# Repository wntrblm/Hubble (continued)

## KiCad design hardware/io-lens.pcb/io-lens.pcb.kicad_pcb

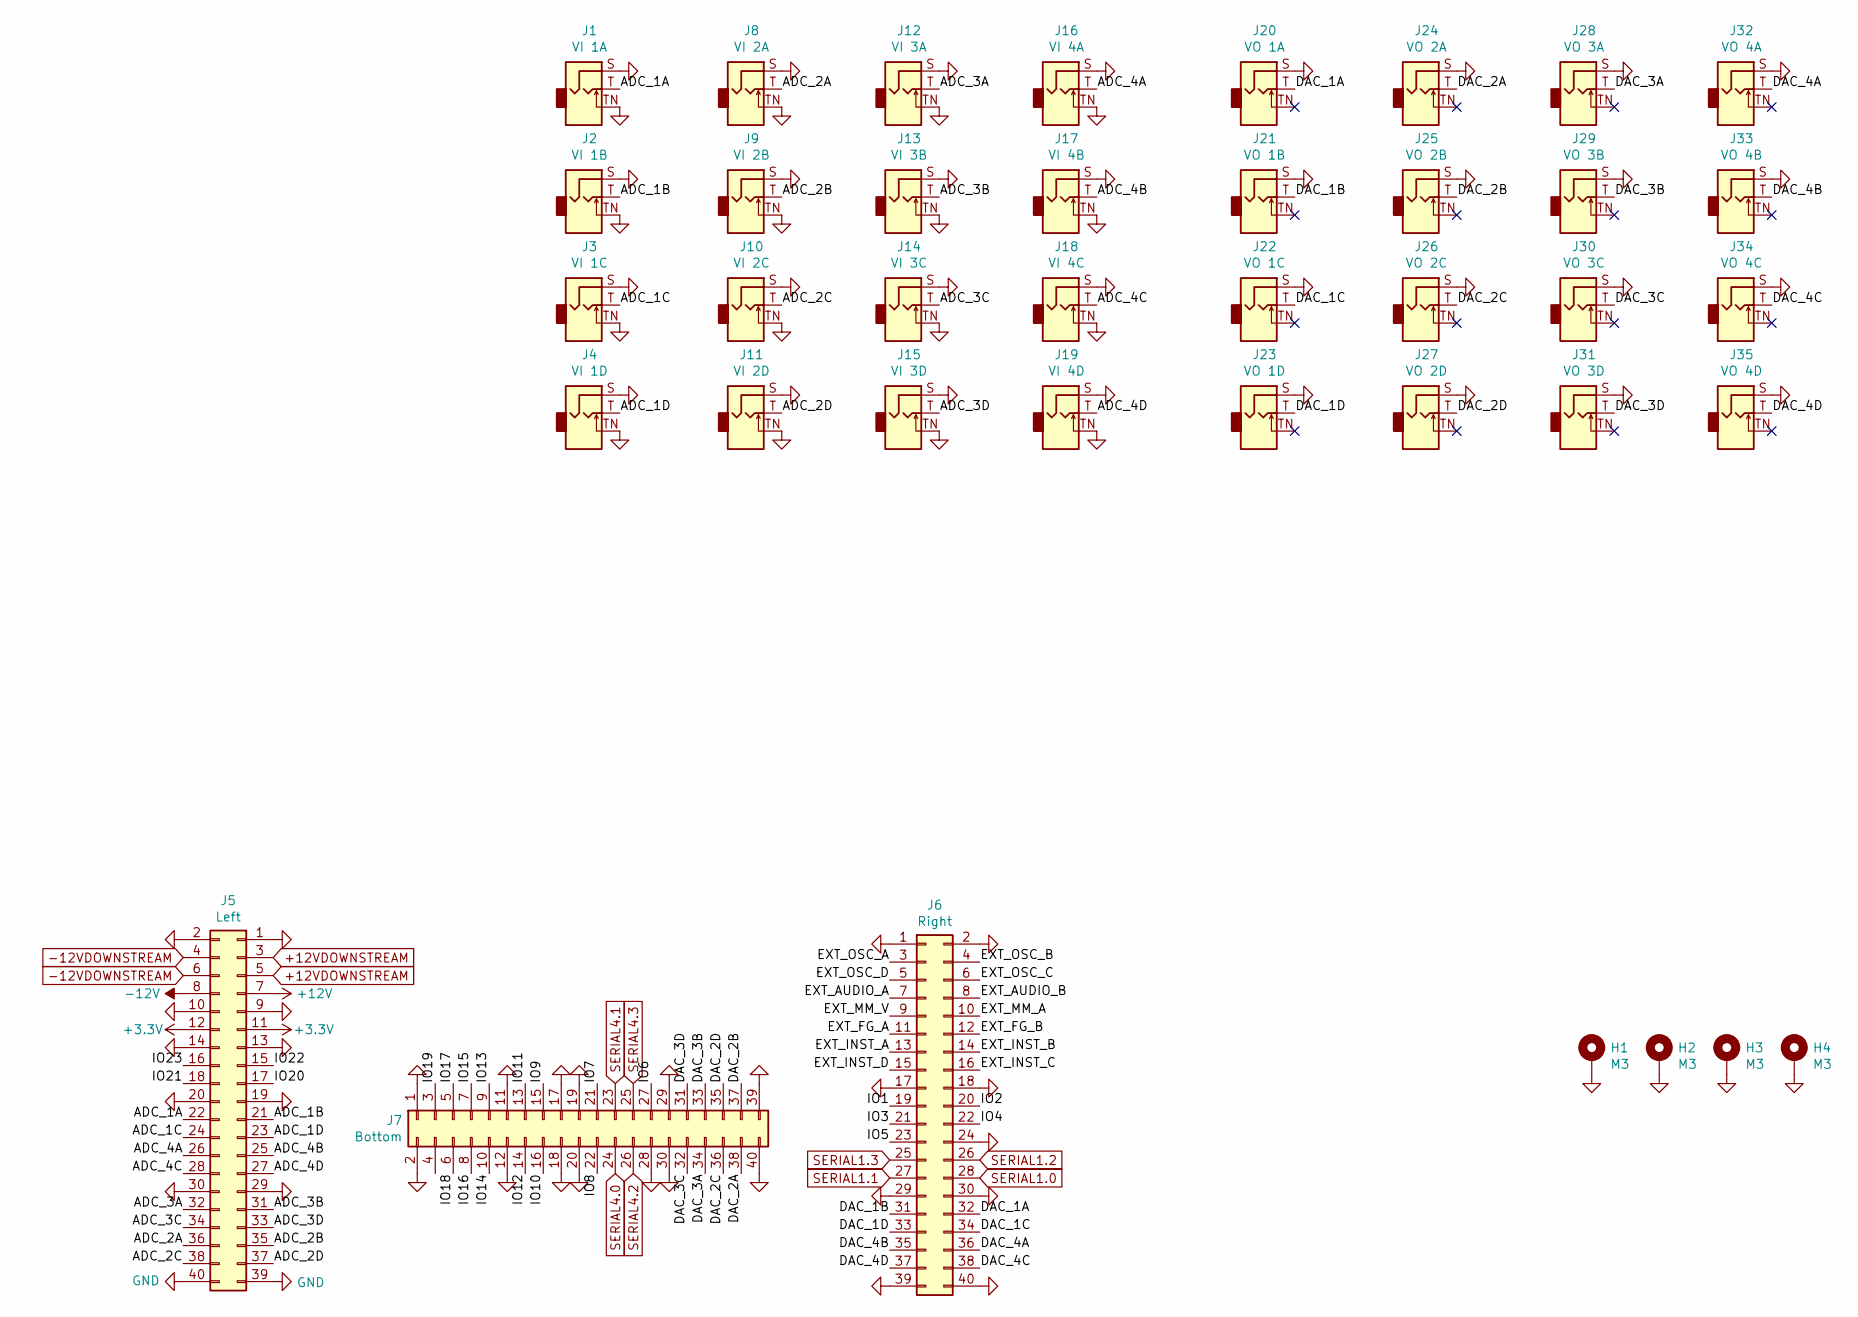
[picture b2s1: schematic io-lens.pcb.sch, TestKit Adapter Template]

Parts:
H1, H2, H3, H4: M3; MountingHole_3.2mm_M3_Pad_Via
J1: VI 1A; WQP-WQP518MA; mpn WQP-WQP518MA
J2: VI 1B; WQP-WQP518MA; mpn WQP-WQP518MA
J3: VI 1C; WQP-WQP518MA; mpn WQP-WQP518MA
J4: VI 1D; WQP-WQP518MA; mpn WQP-WQP518MA
J5: Left; PinSocket_2x20_P2.54mm_Vertical
J6: Right; PinSocket_2x20_P2.54mm_Vertical
J7: Bottom; PinSocket_2x20_P2.54mm_Vertical
J8: VI 2A; WQP-WQP518MA; mpn WQP-WQP518MA
J9: VI 2B; WQP-WQP518MA; mpn WQP-WQP518MA
J10: VI 2C; WQP-WQP518MA; mpn WQP-WQP518MA
J11: VI 2D; WQP-WQP518MA; mpn WQP-WQP518MA
J12: VI 3A; WQP-WQP518MA; mpn WQP-WQP518MA
J13: VI 3B; WQP-WQP518MA; mpn WQP-WQP518MA
J14: VI 3C; WQP-WQP518MA; mpn WQP-WQP518MA
J15: VI 3D; WQP-WQP518MA; mpn WQP-WQP518MA
J16: VI 4A; WQP-WQP518MA; mpn WQP-WQP518MA
J17: VI 4B; WQP-WQP518MA; mpn WQP-WQP518MA
J18: VI 4C; WQP-WQP518MA; mpn WQP-WQP518MA
J19: VI 4D; WQP-WQP518MA; mpn WQP-WQP518MA
J20: VO 1A; WQP-WQP518MA; mpn WQP-WQP518MA
J21: VO 1B; WQP-WQP518MA; mpn WQP-WQP518MA
J22: VO 1C; WQP-WQP518MA; mpn WQP-WQP518MA
J23: VO 1D; WQP-WQP518MA; mpn WQP-WQP518MA
J24: VO 2A; WQP-WQP518MA; mpn WQP-WQP518MA
J25: VO 2B; WQP-WQP518MA; mpn WQP-WQP518MA
J26: VO 2C; WQP-WQP518MA; mpn WQP-WQP518MA
J27: VO 2D; WQP-WQP518MA; mpn WQP-WQP518MA
J28: VO 3A; WQP-WQP518MA; mpn WQP-WQP518MA
J29: VO 3B; WQP-WQP518MA; mpn WQP-WQP518MA
J30: VO 3C; WQP-WQP518MA; mpn WQP-WQP518MA
J31: VO 3D; WQP-WQP518MA; mpn WQP-WQP518MA
J32: VO 4A; WQP-WQP518MA; mpn WQP-WQP518MA
J33: VO 4B; WQP-WQP518MA; mpn WQP-WQP518MA
J34: VO 4C; WQP-WQP518MA; mpn WQP-WQP518MA
J35: VO 4D; WQP-WQP518MA; mpn WQP-WQP518MA

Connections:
+3V3: J5.11, J5.12
+12V: J5.7
+12VDOWNSTREAM: J5.3, J5.5
-12V: J5.8
-12VDOWNSTREAM: J5.4, J5.6
/ADC_1A: J1.T (Tip), J5.22
/ADC_1B: J2.T (Tip), J5.21
/ADC_1C: J3.T (Tip), J5.24
/ADC_1D: J4.T (Tip), J5.23
/ADC_2A: J5.36, J8.T (Tip)
/ADC_2B: J5.35, J9.T (Tip)
/ADC_2C: J5.38, J10.T (Tip)
/ADC_2D: J5.37, J11.T (Tip)
/ADC_3A: J5.32, J12.T (Tip)
/ADC_3B: J5.31, J13.T (Tip)
/ADC_3C: J5.34, J14.T (Tip)
/ADC_3D: J5.33, J15.T (Tip)
/ADC_4A: J5.26, J16.T (Tip)
/ADC_4B: J5.25, J17.T (Tip)
/ADC_4C: J5.28, J18.T (Tip)
/ADC_4D: J5.27, J19.T (Tip)
/DAC_1A: J6.32, J20.T (Tip)
/DAC_1B: J6.31, J21.T (Tip)
/DAC_1C: J6.34, J22.T (Tip)
/DAC_1D: J6.33, J23.T (Tip)
/DAC_2A: J7.38, J24.T (Tip)
/DAC_2B: J7.37, J25.T (Tip)
/DAC_2C: J7.36, J26.T (Tip)
/DAC_2D: J7.35, J27.T (Tip)
/DAC_3A: J7.34, J28.T (Tip)
/DAC_3B: J7.33, J29.T (Tip)
/DAC_3C: J7.32, J30.T (Tip)
/DAC_3D: J7.31, J31.T (Tip)
/DAC_4A: J6.36, J32.T (Tip)
/DAC_4B: J6.35, J33.T (Tip)
/DAC_4C: J6.38, J34.T (Tip)
/DAC_4D: J6.37, J35.T (Tip)
/EXT_AUDIO_A: J6.7
/EXT_AUDIO_B: J6.8
/EXT_FG_A: J6.11
/EXT_FG_B: J6.12
/EXT_INST_A: J6.13
/EXT_INST_B: J6.14
/EXT_INST_C: J6.16
/EXT_INST_D: J6.15
/EXT_MM_A: J6.10
/EXT_MM_V: J6.9
/EXT_OSC_A: J6.3
/EXT_OSC_B: J6.4
/EXT_OSC_C: J6.6
/EXT_OSC_D: J6.5
/IO1: J6.19
/IO2: J6.20
/IO3: J6.21
/IO4: J6.22
/IO5: J6.23
/IO6: J7.27
/IO7: J7.21
/IO8: J7.22
/IO9: J7.15
/IO10: J7.16
/IO11: J7.13
/IO12: J7.14
/IO13: J7.9
/IO14: J7.10
/IO15: J7.7
/IO16: J7.8
/IO17: J7.5
/IO18: J7.6
/IO19: J7.3
/IO20: J5.17
/IO21: J5.18
/IO22: J5.15
/IO23: J5.16
GND: H1.1, H2.1, H3.1, H4.1, J1.S (Sleeve), J1.TN (Tip_normalize), J2.S (Sleeve), J2.TN (Tip_normalize), J3.S (Sleeve), J3.TN (Tip_normalize), J4.S (Sleeve), J4.TN (Tip_normalize), J5.1, J5.2, J5.9, J5.10, J5.13, J5.14, J5.19, J5.20, J5.29, J5.30, J5.39, J5.40, J6.1, J6.2, J6.17, J6.18, J6.24, J6.29, J6.30, J6.39, J6.40, J7.1, J7.2, J7.11, J7.12, J7.17, J7.18, J7.19, J7.20, J7.28, J7.29, J7.30, J7.39, J7.40, J8.S (Sleeve), J8.TN (Tip_normalize), J9.S (Sleeve), J9.TN (Tip_normalize), J10.S (Sleeve), J10.TN (Tip_normalize), J11.S (Sleeve), J11.TN (Tip_normalize), J12.S (Sleeve), J12.TN (Tip_normalize), J13.S (Sleeve), J13.TN (Tip_normalize), J14.S (Sleeve), J14.TN (Tip_normalize), J15.S (Sleeve), J15.TN (Tip_normalize), J16.S (Sleeve), J16.TN (Tip_normalize), J17.S (Sleeve), J17.TN (Tip_normalize), J18.S (Sleeve), J18.TN (Tip_normalize), J19.S (Sleeve), J19.TN (Tip_normalize), J20.S (Sleeve), J21.S (Sleeve), J22.S (Sleeve), J23.S (Sleeve), J24.S (Sleeve), J25.S (Sleeve), J26.S (Sleeve), J27.S (Sleeve), J28.S (Sleeve), J29.S (Sleeve), J30.S (Sleeve), J31.S (Sleeve), J32.S (Sleeve), J33.S (Sleeve), J34.S (Sleeve), J35.S (Sleeve)
SERIAL1.0: J6.28
SERIAL1.1: J6.27
SERIAL1.2: J6.26
SERIAL1.3: J6.25
SERIAL4.0: J7.24
SERIAL4.1: J7.23
SERIAL4.2: J7.26
SERIAL4.3: J7.25

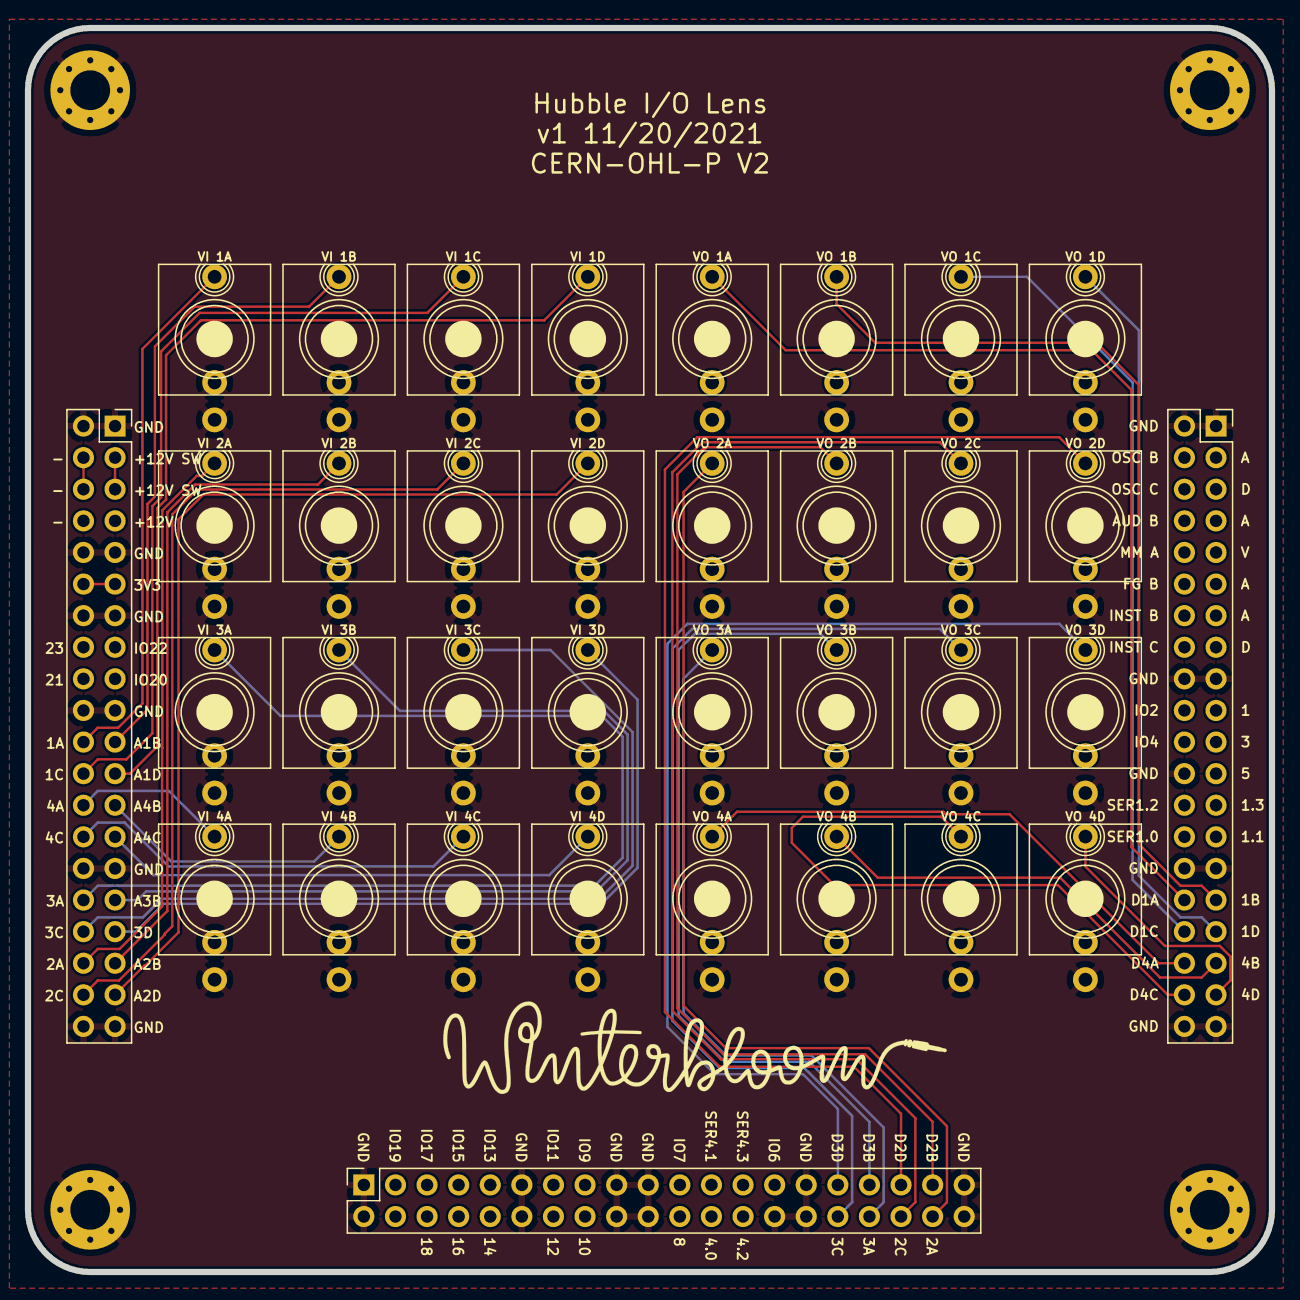
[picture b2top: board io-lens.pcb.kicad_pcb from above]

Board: 2 copper layers, 100.0 x 100.0 mm, 39 parts (0 on the bottom side), 36 nets.

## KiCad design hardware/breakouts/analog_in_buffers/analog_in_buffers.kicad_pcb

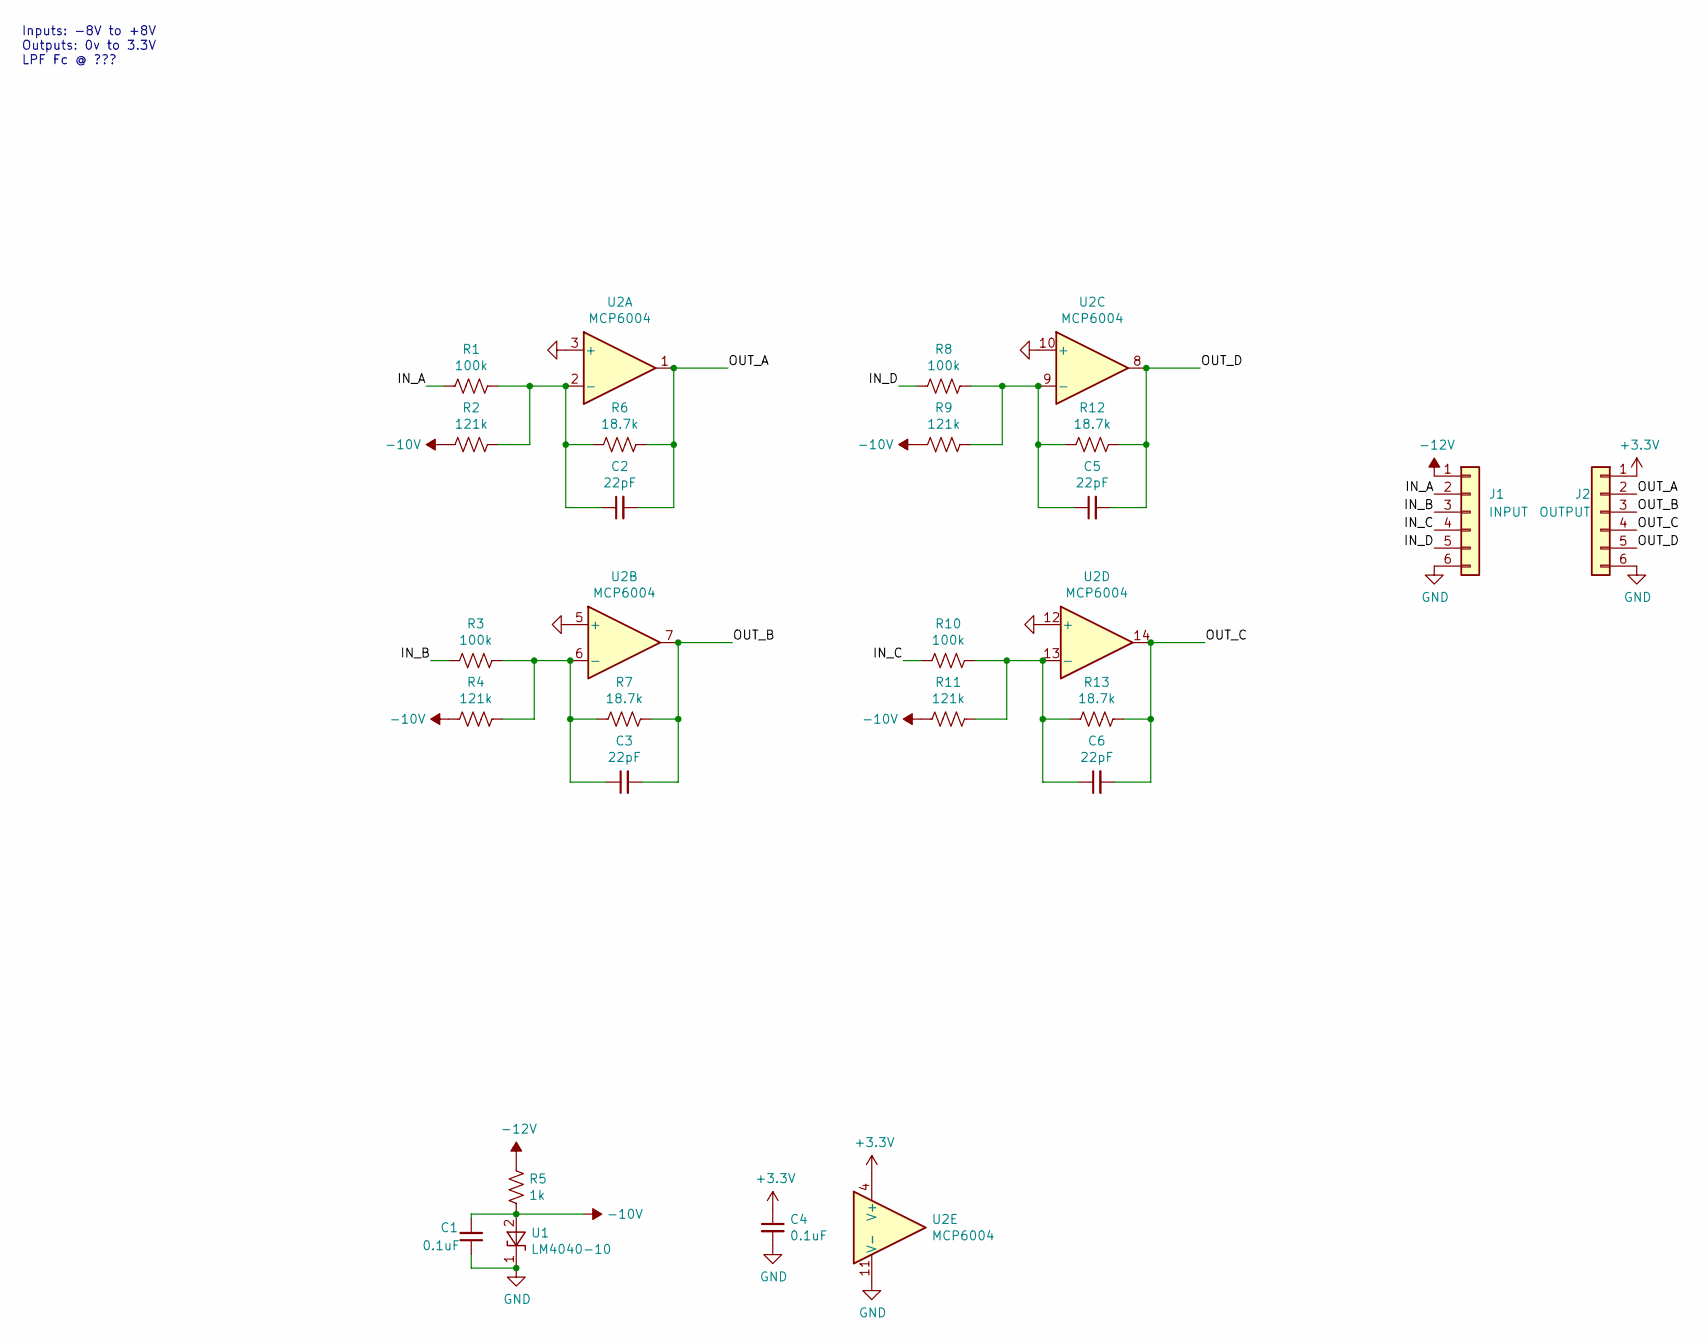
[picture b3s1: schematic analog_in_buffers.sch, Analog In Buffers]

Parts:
C1, C4: 0.1uF; C_0603_1608Metric_Pad1.08x0.95mm_HandSolder
C2, C3, C5, C6: 22pF; C_0603_1608Metric_Pad1.08x0.95mm_HandSolder
J1: INPUT; PinHeader_1x06_P2.54mm_Vertical
J2: OUTPUT; PinHeader_1x06_P2.54mm_Vertical
R1, R3, R8, R10: 100k; R_0603_1608Metric_Pad0.98x0.95mm_HandSolder
R2, R4, R9, R11: 121k; R_0603_1608Metric_Pad0.98x0.95mm_HandSolder
R5: 1k; R_0603_1608Metric_Pad0.98x0.95mm_HandSolder
R6, R7, R12, R13: 18.7k; R_0603_1608Metric_Pad0.98x0.95mm_HandSolder
U1: LM4040-10; SOT-23; mpn LM4040DIM3-10.0/NOPB
U2: MCP6004; TSSOP-14_4.4x5mm_P0.65mm; mpn MCP6004T-I/ST, MCP6004T-E/ST

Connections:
+3V3: C4.1, J2.1, U2.4 (V+)
-10V: C1.2, R2.2, R4.2, R5.1, R9.2, R11.2, U1.2 (A)
-12V: J1.1, R5.2
/IN_A: J1.2, R1.2
/IN_B: J1.3, R3.2
/IN_C: J1.4, R10.2
/IN_D: J1.5, R8.2
/OUT_A: C2.2, J2.2, R6.1, U2.1
/OUT_B: C3.2, J2.3, R7.1, U2.7
/OUT_C: C6.2, J2.4, R13.1, U2.14
/OUT_D: C5.2, J2.5, R12.1, U2.8
GND: C1.1, C4.2, J1.6, J2.6, U1.1 (K), U2.3 (+), U2.5 (+), U2.10 (+), U2.11 (V-), U2.12 (+)
unnamed: C2.1, R1.1, R2.1, R6.2, U2.2 (-)
unnamed: C3.1, R3.1, R4.1, R7.2, U2.6 (-)
unnamed: C5.1, R8.1, R9.1, R12.2, U2.9 (-)
unnamed: C6.1, R10.1, R11.1, R13.2, U2.13 (-)

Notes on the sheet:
Inputs: -8V to +8V Outputs: 0v to 3.3V LPF Fc @ ???

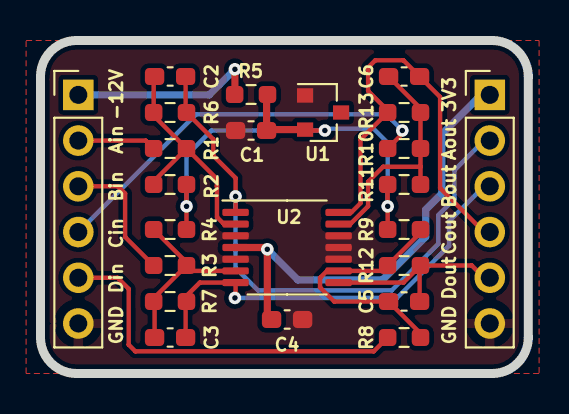
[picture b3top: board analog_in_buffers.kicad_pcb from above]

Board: 2 copper layers, 27.1 x 18.5 mm, 23 parts (0 on the bottom side), 16 nets.

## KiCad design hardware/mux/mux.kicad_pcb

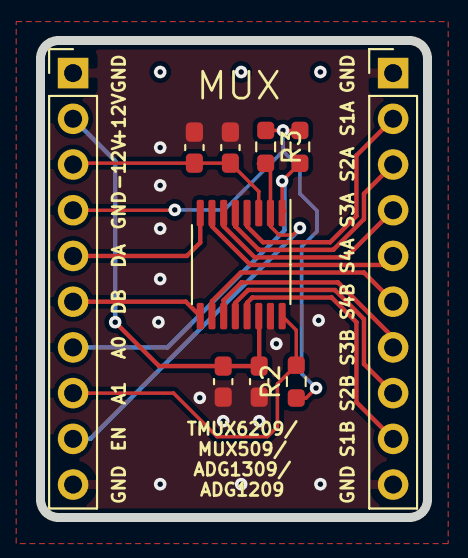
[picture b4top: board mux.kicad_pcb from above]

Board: 2 copper layers, 21.5 x 26.5 mm, 10 parts (0 on the bottom side), 17 nets.

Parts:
C1, C3: 1uF; C_0603_1608Metric_Pad1.08x0.95mm_HandSolder
C2, C4: 0.1uF; C_0603_1608Metric_Pad1.08x0.95mm_HandSolder
J1: Left; PinHeader_1x10_P2.54mm_Vertical
J2: Right; PinHeader_1x10_P2.54mm_Vertical
R1, R2, R3: 10k; R_0603_1608Metric_Pad0.98x0.95mm_HandSolder
U1: TMUX6209; TSSOP-16_4.4x5mm_P0.65mm

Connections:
+3V3: J1.4, R1.1, R2.1, R3.1
+12V: C1.1, C2.1, J1.2, U1.14
-12V: C3.1, C4.1, J1.3, U1.3
/A0: J1.7, R1.2, U1.1
/A1: J1.8, R2.2, U1.16
/DA: J1.5, U1.8
/DB: J1.6, U1.9
/EN: J1.9, R3.2, U1.2
/S1A: J2.2, U1.4
/S1B: J2.9, U1.13
/S2A: J2.3, U1.5
/S2B: J2.8, U1.12
/S3A: J2.4, U1.6
/S3B: J2.7, U1.11
/S4A: J2.5, U1.7
/S4B: J2.6, U1.10
GND: C1.2, C2.2, C3.2, C4.2, J1.1, J1.10, J2.1, J2.10, U1.15

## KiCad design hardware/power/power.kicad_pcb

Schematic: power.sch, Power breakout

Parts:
C1, C2, C3, C4: 10uF; C_0805_2012Metric_Pad1.18x1.45mm_HandSolder
C5, C6: 10uF; CP_Radial_D5.0mm_P2.50mm
D1, D2: BARRIER; D_SOD-123
D3: Blue; LED_D3.0mm
D4: Red; LED_D3.0mm
D5: Green; LED_D3.0mm
D6: Yellow; LED_D3.0mm
FB1, FB2: BEAD; L_0603_1608Metric_Pad1.05x0.95mm_HandSolder
J1: Eurorack_Power; mpn 302-S101
J2: Left power; PinHeader_2x02_P2.54mm_Vertical
J3: Left; PinHeader_1x04_P2.54mm_Vertical
J4: Right; PinHeader_1x04_P2.54mm_Vertical
J5: Right power; PinHeader_2x02_P2.54mm_Vertical
R1, R2: 0.3-22R; R_0805_2012Metric
R3, R4, R5, R6: 1k; R_0603_1608Metric_Pad0.98x0.95mm_HandSolder
SW1: Power; Switch_DPDT_Thonk_DW4_2.54mm_pitch_5.08mm_spacing
U1: LM1117-3.3; SOT-223-3_TabPin2; mpn LM1117IMP-3.3
U2: LM1117-5.0; SOT-223-3_TabPin2; mpn LM1117IMP-3.3

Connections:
+3V3: C3.1, D5.2, J2.2, J2.4, J3.3, J3.4, R1.1, U1.2
+5V: C4.1, D6.2, J4.3, J4.4, R2.1, U2.2
+12V: C1.2, C2.2, C5.1, D3.2, FB1.1, J5.2, J5.4, U1.3, U2.3
-12V: C6.2, D4.1, FB2.1, J5.1, J5.3
/+12VRAW: J1.9 (+12V), J1.10 (+12V), SW1.2
/+12VSWITCHED: D1.2, SW1.1
/-12VRAW: J1.1 (-12V), J1.2 (-12V), SW1.5
/-12VSWITCHED: D2.1, SW1.4
GND: C1.1, C2.1, C3.2, C4.2, C5.2, C6.1, J1.3 (GND), J1.4 (GND), J1.5 (GND), J1.6 (GND), J1.7 (GND), J1.8 (GND), J2.1, J2.3, J3.1, J3.2, J4.1, J4.2, R1.2, R2.2, R3.2, R4.2, R5.2, R6.2, U1.1, U2.1
unnamed: D1.1, FB1.2
unnamed: D2.2, FB2.2
unnamed: D3.1, R3.1
unnamed: D4.2, R4.1
unnamed: D5.1, R5.1
unnamed: D6.1, R6.1

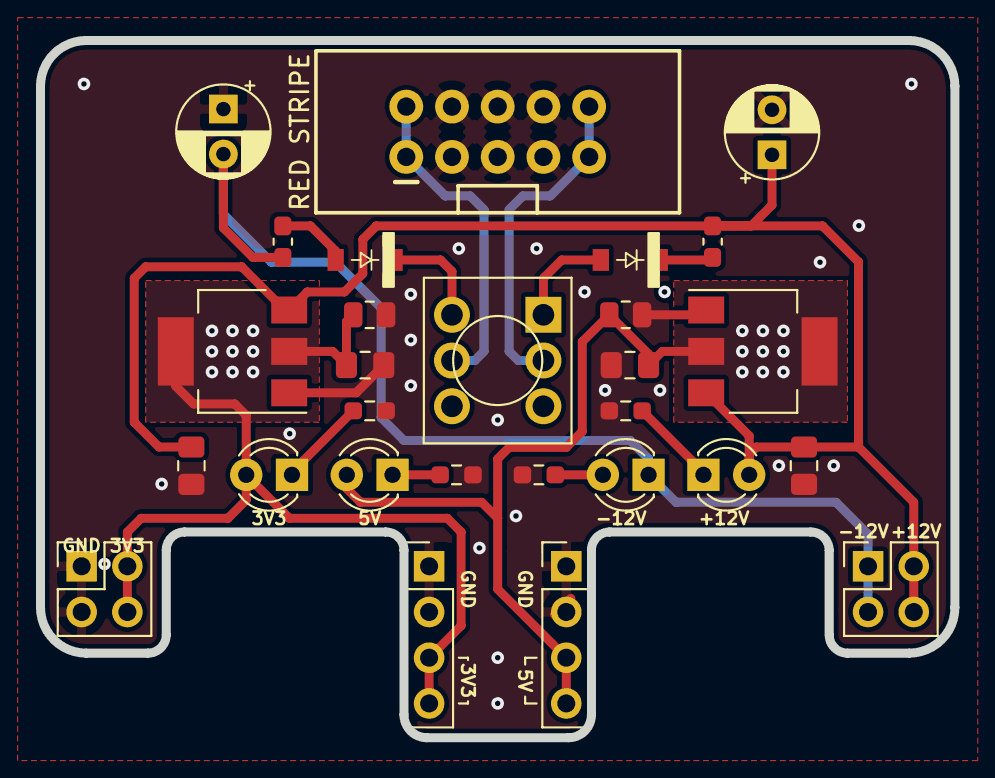
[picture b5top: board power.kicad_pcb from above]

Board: 2 copper layers, 50.8 x 38.7 mm, 28 parts (0 on the bottom side), 15 nets.

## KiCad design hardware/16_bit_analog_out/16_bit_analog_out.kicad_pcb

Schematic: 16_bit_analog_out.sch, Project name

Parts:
C1: 1uF; C_0603_1608Metric_Pad1.08x0.95mm_HandSolder
C2, C3, C4, C5, C6: 0.1uF; C_0603_1608Metric_Pad1.08x0.95mm_HandSolder
FB1: BEAD; L_0603_1608Metric_Pad1.05x0.95mm_HandSolder
J1: Inputs; PinHeader_1x08_P2.54mm_Vertical
J2: Outputs; PinHeader_1x08_P2.54mm_Vertical
R1: 270; R_0603_1608Metric_Pad0.98x0.95mm_HandSolder
R2, R4, R6, R8: 1.54k; R_0603_1608Metric_Pad0.98x0.95mm_HandSolder
R3, R5, R7, R9: 12.4k; R_0603_1608Metric_Pad0.98x0.95mm_HandSolder
R10, R11, R12, R13: 10k; R_0603_1608Metric_Pad0.98x0.95mm_HandSolder
R14, R15, R16, R17: 1k; R_0603_1608Metric_Pad0.98x0.95mm_HandSolder
U1: LM4040-10; SOT-23; mpn LM4040DIM3-10.0/NOPB
U2: AD5685R?RUZ; TSSOP-16_4.4x5mm_P0.65mm; mpn AD5685ARUZ, AD5685BRUZ
U3: OPA4197; TSSOP-14_4.4x5mm_P0.65mm; mpn OPA4197IPW

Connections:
+3.3VA: C1.2, C2.2, FB1.1, U2.5 (VDD)
+3V3: C3.2, FB1.2, J1.3, U2.11 (VLOGIC), U2.15 (~RESET), U2.16 (RSTSEL)
+12V: C5.2, J2.1, U3.4 (V+)
-10V: C4.2, R1.1, R3.2, R5.2, R7.2, R9.2, U1.2 (A)
-12V: C6.2, J2.2, R1.2, U3.11 (V-)
/CS: J1.6, U2.13 (~SYNC)
/DAC_OUT_A: R2.2, U2.3 (VOUTA)
/DAC_OUT_B: R4.2, U2.2 (VOUTB)
/DAC_OUT_C: R6.2, U2.6 (VOUTC)
/DAC_OUT_D: R8.2, U2.7 (VOUTD)
/OUT_A: J2.3, R10.1, R14.1
/OUT_B: J2.4, R11.1, R15.1
/OUT_C: J2.5, R12.1, R16.1
/OUT_D: J2.6, R13.1, R17.1
/SCLK: J1.4, U2.12 (SCLK)
/SDI: J1.5, U2.14 (SDIN)
/SDO: J1.7, U2.8 (SDO)
/VREF: J2.7, U2.1 (VREF)
GND: C1.1, C2.1, C3.1, C4.1, C5.1, C6.1, J1.1, J1.2, J1.8, J2.8, U1.1 (K), U2.4 (GND), U2.9 (~LDAC), U2.10 (GAIN), U3.3 (+), U3.5 (+), U3.10 (+), U3.12 (+)
unnamed: R2.1, R3.1, R10.2, U3.2 (-)
unnamed: R4.1, R5.1, R11.2, U3.6 (-)
unnamed: R6.1, R7.1, R12.2, U3.9 (-)
unnamed: R8.1, R9.1, R13.2, U3.13 (-)
unnamed: R14.2, U3.1
unnamed: R15.2, U3.7
unnamed: R16.2, U3.8
unnamed: R17.2, U3.14

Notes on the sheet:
Amplifies 0 V - 2.5 V to -8 V to 8 V Resolution: - 16-bit DAC: 0.25 mV - 14-bit DAC: 1 mV

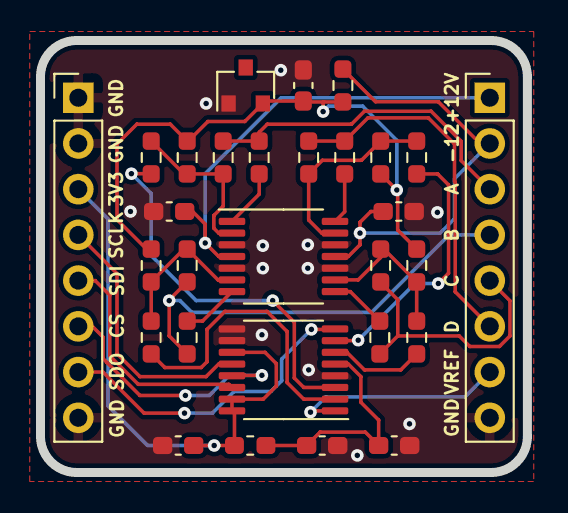
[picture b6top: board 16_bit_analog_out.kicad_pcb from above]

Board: 2 copper layers, 27.1 x 24.0 mm, 29 parts (0 on the bottom side), 27 nets.

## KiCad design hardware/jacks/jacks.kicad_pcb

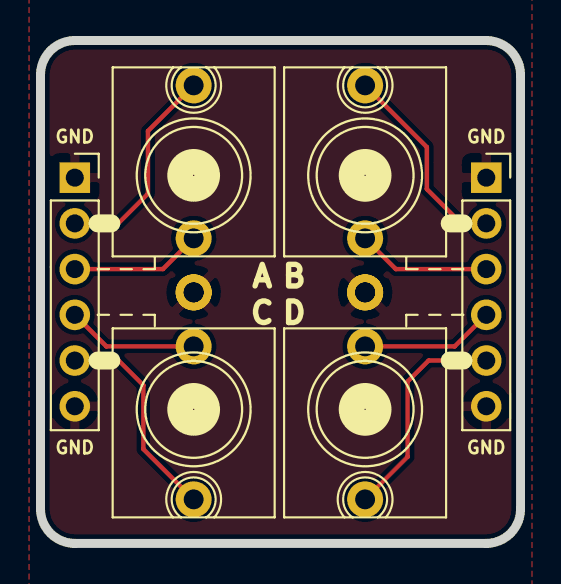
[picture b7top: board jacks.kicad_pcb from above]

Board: 2 copper layers, 26.7 x 27.9 mm, 6 parts (0 on the bottom side), 9 nets.

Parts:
J1: Left; PinSocket_1x06_P2.54mm_Vertical
J2: A; WQP-WQP518MA
J3: B; WQP-WQP518MA
J4: C; WQP-WQP518MA
J5: D; WQP-WQP518MA
J6: Right; PinSocket_1x06_P2.54mm_Vertical

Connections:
GND: J1.1, J1.6, J2.S, J3.S, J4.S, J5.S, J6.1, J6.6
unnamed: J1.2, J2.T
unnamed: J1.3, J2.TN
unnamed: J1.4, J4.TN
unnamed: J1.5, J4.T
unnamed: J3.T, J6.2
unnamed: J3.TN, J6.3
unnamed: J5.T, J6.5
unnamed: J5.TN, J6.4

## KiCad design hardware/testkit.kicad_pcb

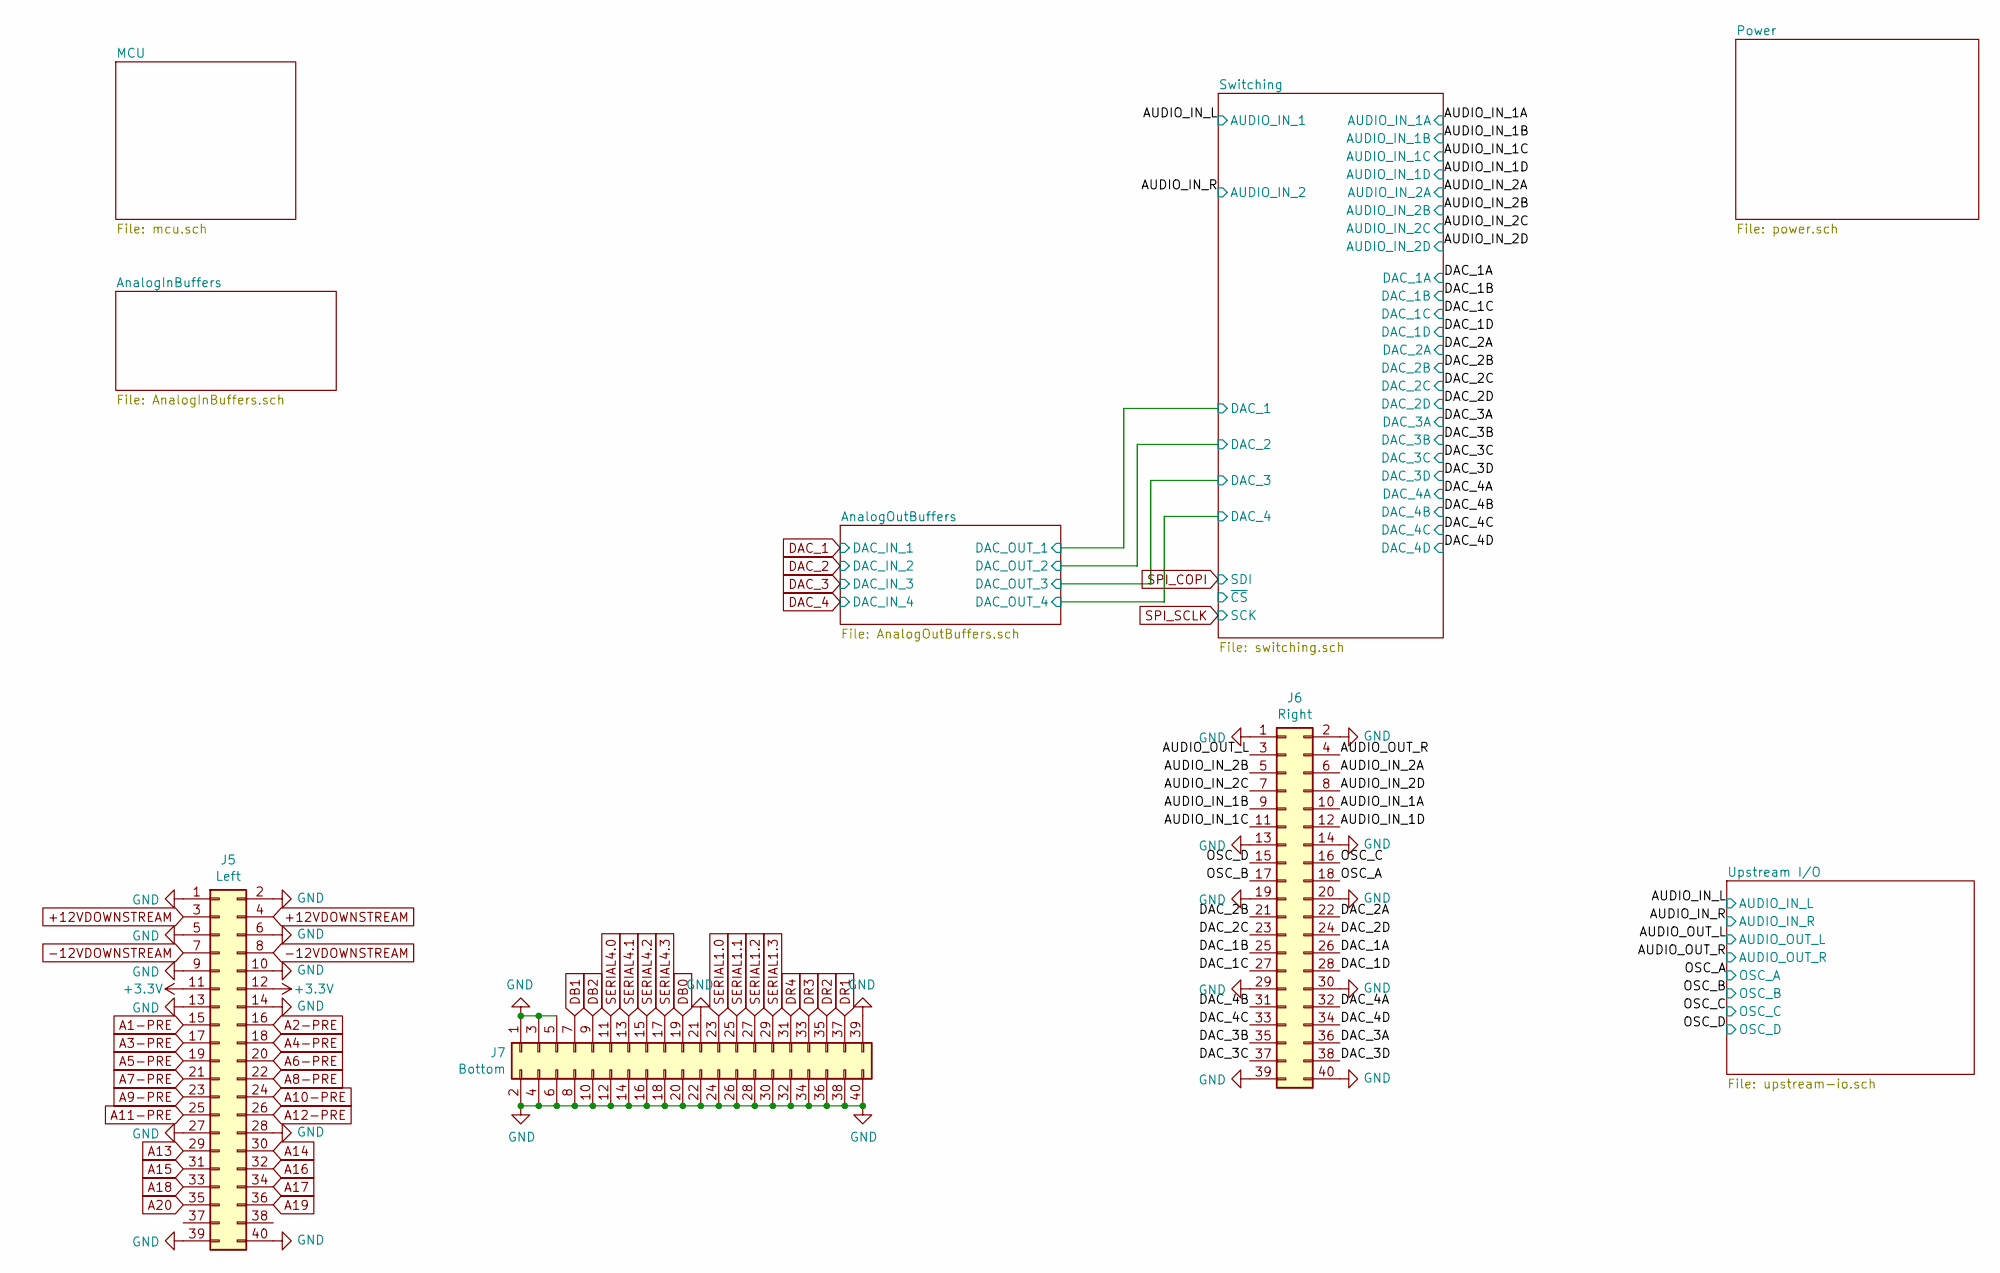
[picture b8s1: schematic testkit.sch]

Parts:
J5: Left; PinSocket_2x20_P2.54mm_Vertical
J6: Right; PinSocket_2x20_P2.54mm_Vertical
J7: Bottom; PinSocket_2x20_P2.54mm_Vertical

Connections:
+12VDOWNSTREAM: J5.3, J5.4; also elsewhere on the board
-12VDOWNSTREAM: J5.7, J5.8; also elsewhere on the board
/AUDIO_IN_1A: J6.10; also elsewhere on the board
/AUDIO_IN_1B: J6.9; also elsewhere on the board
/AUDIO_IN_1C: J6.11; also elsewhere on the board
/AUDIO_IN_1D: J6.12; also elsewhere on the board
/AUDIO_IN_2A: J6.6; also elsewhere on the board
/AUDIO_IN_2B: J6.5; also elsewhere on the board
/AUDIO_IN_2C: J6.7; also elsewhere on the board
/AUDIO_IN_2D: J6.8; also elsewhere on the board
/AUDIO_OUT_L: J6.3; also elsewhere on the board
/AUDIO_OUT_R: J6.4; also elsewhere on the board
/DAC_1A: J6.26; also elsewhere on the board
/DAC_1B: J6.25; also elsewhere on the board
/DAC_1C: J6.27; also elsewhere on the board
/DAC_1D: J6.28; also elsewhere on the board
/DAC_2A: J6.22; also elsewhere on the board
/DAC_2B: J6.21; also elsewhere on the board
/DAC_2C: J6.23; also elsewhere on the board
/DAC_2D: J6.24; also elsewhere on the board
/DAC_3A: J6.36; also elsewhere on the board
/DAC_3B: J6.35; also elsewhere on the board
/DAC_3C: J6.37; also elsewhere on the board
/DAC_3D: J6.38; also elsewhere on the board
/DAC_4A: J6.32; also elsewhere on the board
/DAC_4B: J6.31; also elsewhere on the board
/DAC_4C: J6.33; also elsewhere on the board
/DAC_4D: J6.34; also elsewhere on the board
/OSC_A: J6.18; also elsewhere on the board
/OSC_B: J6.17; also elsewhere on the board
/OSC_C: J6.16; also elsewhere on the board
/OSC_D: J6.15; also elsewhere on the board
A1-PRE: J5.15; also elsewhere on the board
A2-PRE: J5.16; also elsewhere on the board
A3-PRE: J5.17; also elsewhere on the board
A4-PRE: J5.18; also elsewhere on the board
A5-PRE: J5.19; also elsewhere on the board
A6-PRE: J5.20; also elsewhere on the board
A7-PRE: J5.21; also elsewhere on the board
A8-PRE: J5.22; also elsewhere on the board
A9-PRE: J5.23; also elsewhere on the board
A10-PRE: J5.24; also elsewhere on the board
A11-PRE: J5.25; also elsewhere on the board
A12-PRE: J5.26; also elsewhere on the board
A13: J5.29; also elsewhere on the board
A14: J5.30; also elsewhere on the board
A15: J5.31; also elsewhere on the board
A16: J5.32; also elsewhere on the board
A17: J5.34; also elsewhere on the board
A18: J5.33; also elsewhere on the board
A19: J5.36; also elsewhere on the board
A20: J5.35; also elsewhere on the board
DB0: J7.19; also elsewhere on the board
DB1: J7.7; also elsewhere on the board
DB2: J7.9; also elsewhere on the board
DR1: J7.37; also elsewhere on the board
DR2: J7.35; also elsewhere on the board
DR3: J7.33; also elsewhere on the board
DR4: J7.31; also elsewhere on the board
GND: J5.1, J5.2, J5.5, J5.6, J5.9, J5.10, J5.13, J5.14, J5.27, J5.28, J5.39, J5.40, J6.1, J6.2, J6.13, J6.14, J6.19, J6.20, J6.29, J6.30, J6.39, J6.40, J7.1, J7.2, J7.3, J7.4, J7.5, J7.6, J7.8, J7.10, J7.12, J7.14, J7.16, J7.18, J7.20, J7.21, J7.22, J7.24, J7.26, J7.28, J7.30, J7.32, J7.34, J7.36, J7.38, J7.39, J7.40; also elsewhere on the board
SERIAL1.0: J7.23; also elsewhere on the board
SERIAL1.1: J7.25; also elsewhere on the board
SERIAL1.2: J7.27; also elsewhere on the board
SERIAL1.3: J7.29; also elsewhere on the board
SERIAL4.0: J7.11; also elsewhere on the board
SERIAL4.1: J7.13; also elsewhere on the board
SERIAL4.2: J7.15; also elsewhere on the board
SERIAL4.3: J7.17; also elsewhere on the board

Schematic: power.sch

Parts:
C1, C4: 4.7uF; C_0805_2012Metric_Pad1.18x1.45mm_HandSolder
C2, C3, C5: 0.1uF; C_0603_1608Metric_Pad1.08x0.95mm_HandSolder
D1, D2: 1N5819; D_SOD-123
FB1, FB2: 1A; L_0603_1608Metric_Pad1.05x0.95mm_HandSolder
J1: Power; PinHeader_2x05_P2.54mm_Horizontal; mpn 302-S101
R1, R2: 1R; R_1210_3225Metric_Pad1.30x2.65mm_HandSolder; mpn RC2010FK-071RL
R3: 270; R_0603_1608Metric_Pad0.98x0.95mm_HandSolder
SW1: POWER; PinSocket_2x02_P2.54mm_Vertical
U1, U2: INA219BxDCN; SOT-23-8
U3: TLV76733; TI-DGN-HVSSOP-8_3.0x3.0mm_P0.65mm; mpn TLV76733DGNR
U4: LM4040-10; SOT-23; mpn LM4040DIM3-10.0/NOPB

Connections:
+12V: C1.1, D2.1 (K), U3.8 (IN); also elsewhere on the board
+12VDOWNSTREAM: SW1.4; also elsewhere on the board
+12VMONITORED: R1.2, SW1.3, U1.2 (IN-)
+12VRAW: FB1.1, J1.9, J1.10, R1.1, U1.1 (IN+)
-10V: C5.2, R3.2, U4.2 (A); also elsewhere on the board
-12V: D1.2 (A), R3.1; also elsewhere on the board
-12VDOWNSTREAM: SW1.2; also elsewhere on the board
-12VMONITORED: R2.1, SW1.1, U2.1 (IN+)
-12VRAW: FB2.1, J1.1, J1.2, R2.2, U2.2 (IN-)
GND: C1.2, C2.1, C3.1, C4.2, C5.1, J1.3, J1.4, J1.5, J1.6, J1.7, J1.8, U1.3 (GND), U1.7 (A0), U1.8 (A1), U2.3 (GND), U2.7 (A0), U3.4 (GND), U3.6 (GND), U3.9 (PAD), U4.1 (K); also elsewhere on the board
I2C_SCL: U1.5 (SCL), U2.5 (SCL); also elsewhere on the board
I2C_SDA: U1.6 (SDA), U2.6 (SDA); also elsewhere on the board
unnamed: D1.1 (K), FB2.2
unnamed: D2.2 (A), FB1.2

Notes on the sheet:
TODO: Calculate current requirements
Maybe raise to 2A?

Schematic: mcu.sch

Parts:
C6, C9, C11, C12, C13, C14, C15, C16: 0.1uF; C_0603_1608Metric_Pad1.08x0.95mm_HandSolder
C7, C8: 22pF; C_0603_1608Metric_Pad1.08x0.95mm_HandSolder
C10: 4.7uF; C_0603_1608Metric_Pad1.08x0.95mm_HandSolder
C17: 1uF; C_0603_1608Metric_Pad1.08x0.95mm_HandSolder
D3: Dotstar; Dotstar_5050; mpn SK9822
FB3, FB4: 300mA; L_0603_1608Metric_Pad1.05x0.95mm_HandSolder
J3: USB_B; USB_B_OST_USB-B1HSxx_Horizontal
J4: Tag-Connect_SWD_TC2030; Tag_Connect_TC2030NL
R4: 10k; R_0603_1608Metric_Pad0.98x0.95mm_HandSolder
R59, R60: 1k; R_0603_1608Metric_Pad0.98x0.95mm_HandSolder
SW2: Reset; Tactile_Switch_4.2mm; mpn MF-SW-TACT-4.2MM, MF-SW-TACT-6MM
U5: ATSAMD51J20A-M; QFN-64-1EP_9x9mm_P0.5mm_EP3.8x3.8mm; mpn ATSAMD51J20A-M
U6: AD5685R?RUZ; TSSOP-16_4.4x5mm_P0.65mm; mpn AD5685ARUZ, AD5685BRUZ
Y1: 32.768 kHz; Crystal_SMD_2012-2Pin_2.0x1.2mm_HandSoldering

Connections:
/MCU/DAC_CS: U5.31 (PA14), U6.13 (~SYNC)
/MCU/DOTSTAR_CI: D3.2 (CI), U5.44 (PA23)
/MCU/DOTSTAR_DI: D3.1 (DI), U5.43 (PA22)
/MCU/PA27: U5.51 (PA27)
/MCU/PB22: U5.49 (PB22)
/MCU/PB23: U5.50 (PB23)
/MCU/RESET: J4.3 (RESET), R4.1, SW2.1, U5.52 (~RESET)
/MCU/SWCLK: J4.4 (SWCLK), U5.57 (PA30)
/MCU/SWDIO: J4.2 (SWDIO), U5.58 (PA31)
/MCU/VDDANA: C6.1, FB3.1, U5.8 (VDDANA)
/MCU/VDDCORE: C9.1, C10.1, U5.53 (VDDCORE)
/MCU/XIN: C7.2, U5.1 (PA00), Y1.1
/MCU/XOUT: C8.2, U5.2 (PA01), Y1.2
A1: U5.61 (PB00); also elsewhere on the board
A2: U5.62 (PB01); also elsewhere on the board
A3: U5.63 (PB02); also elsewhere on the board
A4: U5.64 (PB03); also elsewhere on the board
A5: U5.3 (PA02); also elsewhere on the board
A6: U5.4 (PA03); also elsewhere on the board
A7: U5.5 (PB04); also elsewhere on the board
A8: U5.6 (PB05); also elsewhere on the board
A9: U5.9 (PB06); also elsewhere on the board
A10: U5.10 (PB07); also elsewhere on the board
A11: U5.11 (PB08); also elsewhere on the board
A12: U5.12 (PB09); also elsewhere on the board
A13: U5.13 (PA04); also elsewhere on the board
A14: U5.14 (PA05); also elsewhere on the board
A15: U5.15 (PA06); also elsewhere on the board
A16: U5.16 (PA07); also elsewhere on the board
A17: U5.18 (PA09); also elsewhere on the board
A18: U5.17 (PA08); also elsewhere on the board
A19: U5.20 (PA11); also elsewhere on the board
A20: U5.19 (PA10); also elsewhere on the board
D+: J3.3, U5.46 (PA25)
D-: J3.2, U5.45 (PA24)
DAC_1: U6.3 (VOUTA); also elsewhere on the board
DAC_2: U6.2 (VOUTB); also elsewhere on the board
DAC_3: U6.6 (VOUTC); also elsewhere on the board
DAC_4: U6.7 (VOUTD); also elsewhere on the board
DB0: U5.29 (PA12); also elsewhere on the board
DB1: U5.23 (PB10); also elsewhere on the board
DB2: U5.24 (PB11); also elsewhere on the board
DR1: U5.42 (PA21); also elsewhere on the board
DR2: U5.41 (PA20); also elsewhere on the board
DR3: U5.40 (PB17); also elsewhere on the board
DR4: U5.39 (PB16); also elsewhere on the board
GND: C6.2, C7.1, C8.1, C9.2, C10.2, C11.2, C12.2, C13.2, C14.2, C15.2, C16.2, C17.2, D3.3 (GND), J3.4, J3.5, J4.5 (GND), SW2.2, U5.7 (GND), U5.22 (GND), U5.33 (GND), U5.47 (GND), U5.54 (GND), U5.65 (EP), U6.4 (GND), U6.9 (~LDAC), U6.10 (GAIN); also elsewhere on the board
I2C_SCL: R60.2, U5.60 (PB31); also elsewhere on the board
I2C_SDA: R59.2, U5.59 (PB30); also elsewhere on the board
unnamed: C16.1, C17.1, FB4.1, U6.5 (VDD)
SERIAL1.0: U5.35 (PA16); also elsewhere on the board
SERIAL1.1: U5.36 (PA17); also elsewhere on the board
SERIAL1.2: U5.37 (PA18); also elsewhere on the board
SERIAL1.3: U5.38 (PA19); also elsewhere on the board
SERIAL4.0: U5.25 (PB12); also elsewhere on the board
SERIAL4.1: U5.26 (PB13); also elsewhere on the board
SERIAL4.2: U5.27 (PB14); also elsewhere on the board
SERIAL4.3: U5.28 (PB15); also elsewhere on the board
SPI_COPI: U5.32 (PA15), U6.14 (SDIN); also elsewhere on the board
SPI_SCLK: U5.30 (PA13), U6.12 (SCLK); also elsewhere on the board

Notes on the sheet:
Required, see Errata CHIP003-159
Check datasheet for proper shield connection
3.0, 3.1 used by dotstar
2.1, 2.2, 2.3 used by DAC
5.0, 5.1 used by I2C
